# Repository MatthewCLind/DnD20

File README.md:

# DnD20
WiFi Connected electronic die for enhancing online DnD gameplaying

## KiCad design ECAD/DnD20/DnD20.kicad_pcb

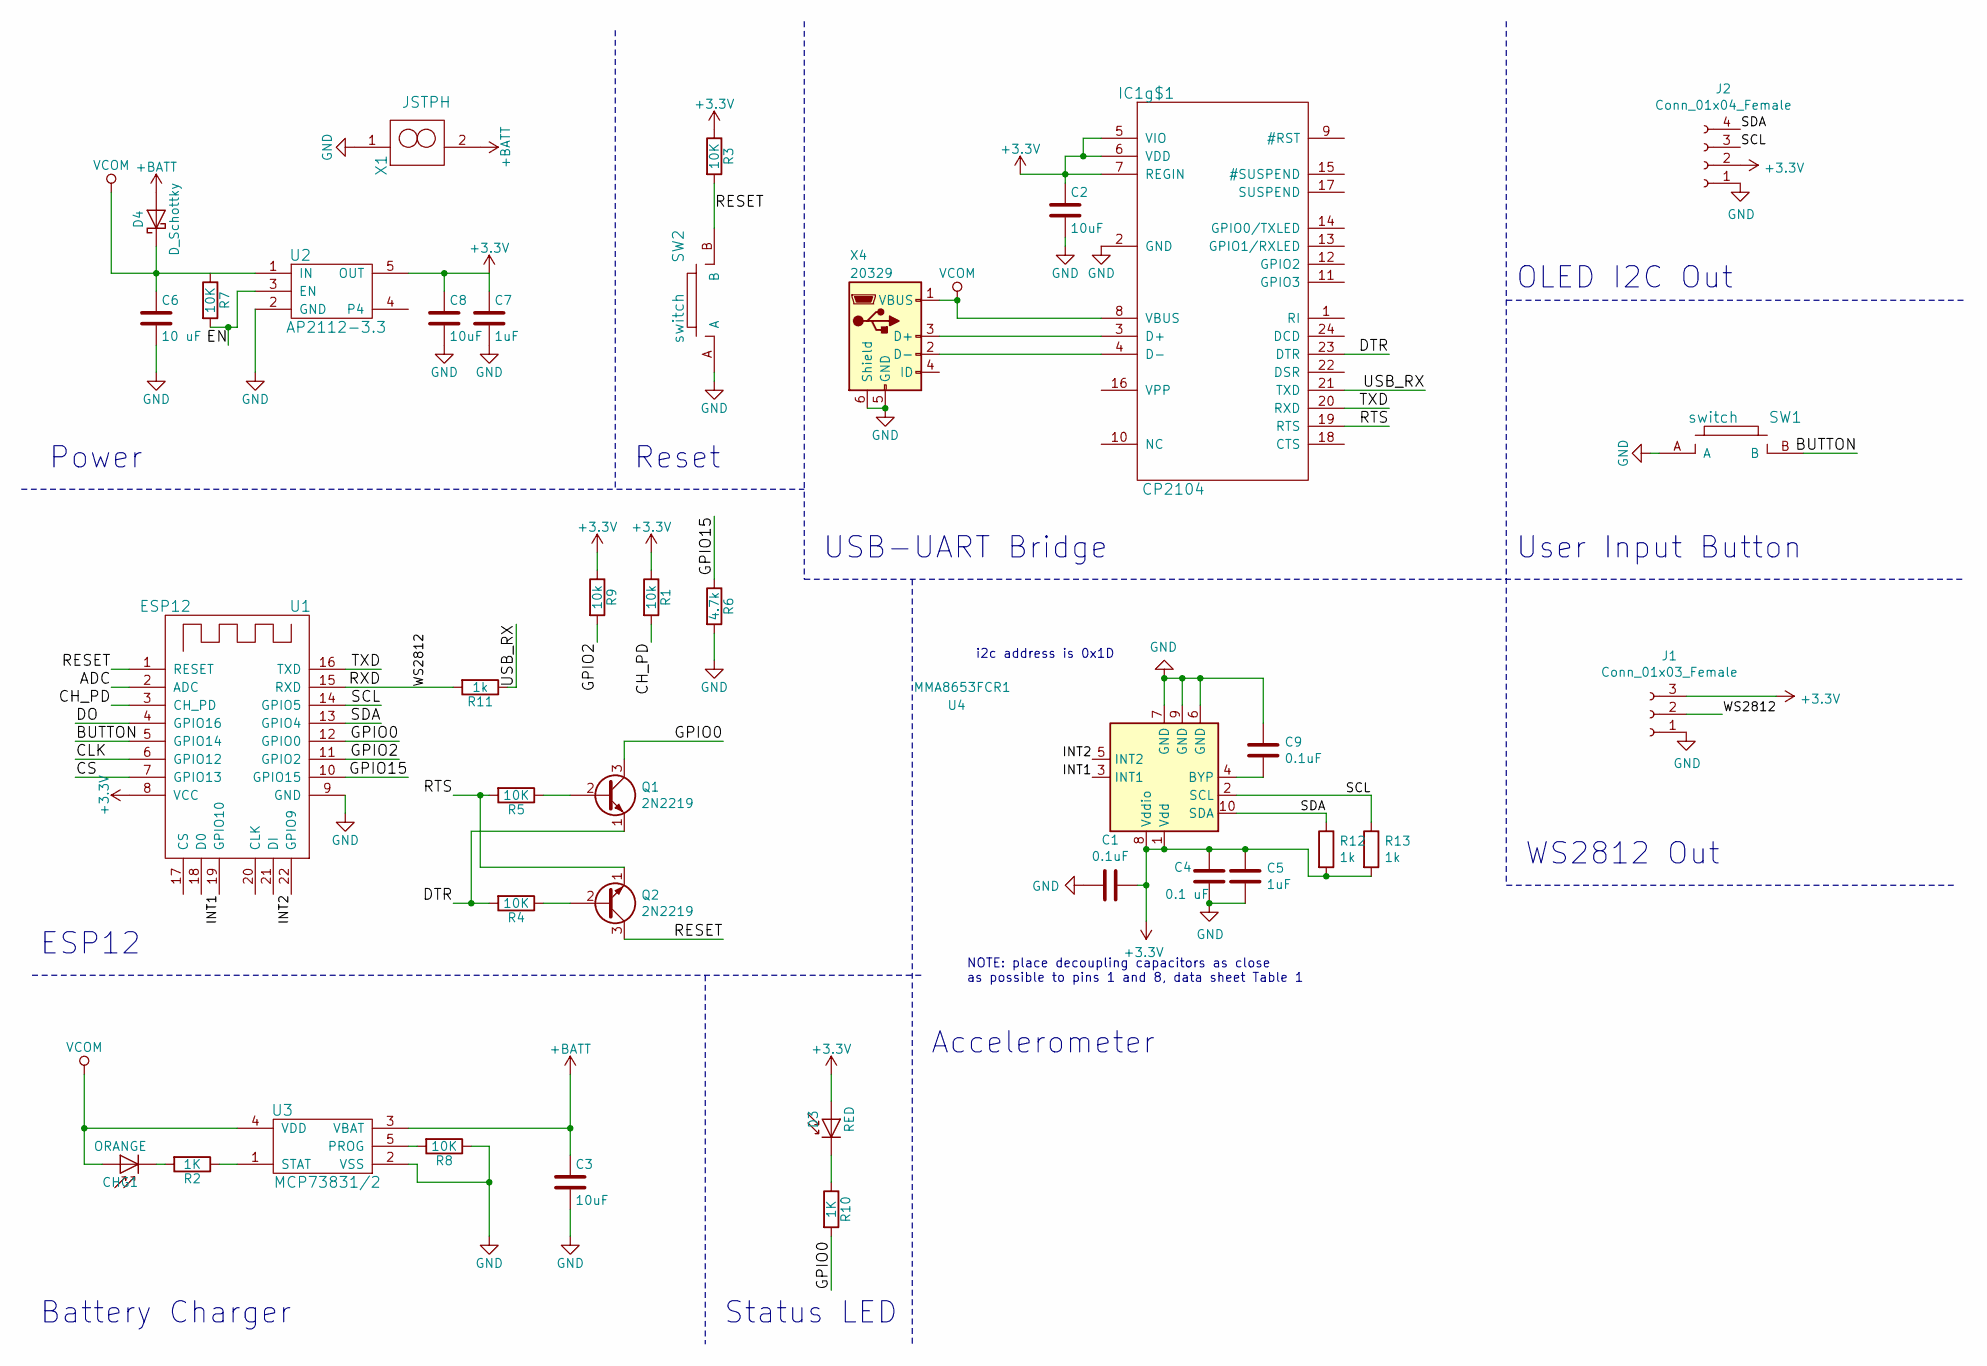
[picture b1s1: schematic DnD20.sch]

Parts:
C1, C9: 0.1uF; C_0805_2012Metric
C2, C3, C8: 10uF; C_0805_2012Metric
C4: 0.1 uF; C_0805_2012Metric
C5, C7: 1uF; C_0805_2012Metric
C6: 10 uF; C_0805_2012Metric
CHG1: ORANGE; LED_0603_1608Metric
D3: RED; LED_0603_1608Metric
D4: D_Schottky; D_T-1_P5.08mm_Horizontal
IC1g$1: CP2104; QFN-24-1EP_4x4mm_P0.5mm_EP2.7x2.7mm
J1: Conn_01x03_Female; PinHeader_1x03_P2.54mm_Vertical
J2: Conn_01x04_Female; PinHeader_1x04_P2.54mm_Vertical
Q1, Q2: 2N2219; TO-39-3
R1, R9: 10k; R_0805_2012Metric
R2, R10: 1K; R_0805_2012Metric
R3, R4, R5, R7, R8: 10K; R_0805_2012Metric
R6: 4.7k; R_0805_2012Metric
R11, R12, R13: 1k; R_0805_2012Metric
SW1, SW2: switch; clicky_button
U1: ESP12; ESP-12E_SMD
U2: AP2112-3.3; SOT-23-5_HandSoldering
U3: MCP73831/2; SOT-23-5_HandSoldering
U4: MMA8653FCR1; DFN-10_2x2mm_P0.4mm
X1: JSTPH; JST_PH_S2B-PH-K_1x02_P2.00mm_Horizontal
X4: 20329; USB_Micro-B_Wuerth_629105150521

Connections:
+3V3: C1.1, C2.1, C4.2, C5.1, C7.1, C8.1, D3.2 (A), IC1g$1.5 (VIO), IC1g$1.6 (VDD), IC1g$1.7 (REGIN), J1.3, J2.2, R1.1, R3.1, R9.1, R12.2, R13.2, U1.8 (VCC), U2.5 (OUT), U4.1 (Vdd), U4.8 (Vddio)
+BATT: C3.1, D4.2 (A), U3.3 (VBAT), X1.2
/ADC: U1.2 (ADC)
/BUTTON: SW1.B, U1.5 (GPIO14)
/CH_PD: R1.2, U1.3 (CH_PD)
/CLK: U1.6 (GPIO12)
/CS: U1.7 (GPIO13)
/DO: U1.4 (GPIO16)
/DTR: IC1g$1.23 (DTR), Q1.1 (E), R4.2
/EN: R7.2, U2.3 (EN)
/GPIO0: Q1.3 (C), R10.2, U1.12 (GPIO0)
/GPIO2: R9.2, U1.11 (GPIO2)
/GPIO15: R6.1, U1.10 (GPIO15)
/INT1: U1.19 (GPIO10), U4.3 (INT1)
/INT2: U1.22 (GPIO9), U4.5 (INT2)
/RESET: Q2.3 (C), R3.2, SW2.B, U1.1 (RESET)
/RTS: IC1g$1.19 (RTS), Q2.1 (E), R5.2
/RXD: J1.2, R11.2, U1.15 (RXD)
/SCL: J2.3, R13.1, U1.14 (GPIO5), U4.2 (SCL)
/SDA: J2.4, R12.1, U1.13 (GPIO4), U4.10 (SDA)
/TXD: IC1g$1.20 (RXD), U1.16 (TXD)
/USB_RX: IC1g$1.21 (TXD), R11.1
GND: C1.2, C2.2, C3.2, C4.1, C5.2, C6.2, C7.2, C8.2, C9.1, IC1g$1.2 (GND), J1.1, J2.1, R6.2, R8.1, SW1.A, SW2.A, U1.9 (GND), U2.2 (GND), U3.2 (VSS), U4.6 (GND), U4.7 (GND), U4.9 (GND), X1.1, X4.5 (GND), X4.6 (Shield)
unnamed: C9.2, U4.4 (BYP)
unnamed: CHG1.1 (K), R2.2
unnamed: D3.1 (K), R10.1
unnamed: IC1g$1.3 (D+), X4.3 (D+)
unnamed: IC1g$1.4 (D-), X4.2 (D-)
unnamed: Q1.2 (B), R5.1
unnamed: Q2.2 (B), R4.1
unnamed: R2.1, U3.1 (STAT)
unnamed: R8.2, U3.5 (PROG)
VCOM: C6.1, CHG1.2 (A), D4.1 (K), IC1g$1.8 (VBUS), U2.1 (IN), U3.4 (VDD), X4.1 (VBUS)

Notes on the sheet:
NOTE: place decoupling capacitors as close as possible to pins 1 and 8, data sheet Table 1
i2c address is 0x1D
Power
ESP12
Battery Charger
USB-UART Bridge
OLED I2C Out
User Input Button
WS2812 Out
Accelerometer
Reset
Status LED

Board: 2 copper layers, 38 parts (2 on the bottom side), 29 nets, no tracks yet.

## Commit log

2018-10-05 dev-log-1
2018-10-05 added first whiteboard sketch
2018-10-05 intial firmware outline
2018-10-05 initial bare-bones webpage html
2018-10-05 added LED feature
2018-10-05 added LEDs and fixedcompiler errors
2018-10-06 updated to work with adafruit feather huzzah
2018-10-06 added second dlog and folders
2018-10-07 added OLED and WiFi code
2018-10-07 changed file extensions to .md
2018-10-08 accelerometer, https request
2018-10-08 formatting
2018-10-08 removed redundant device initalisor
2018-10-08 added Benchtop Prototype showcase
2018-10-08 fixed italics
2018-10-08 added spaces
2018-10-09 fixed date
2018-10-09 new log
2018-10-09 new design drawing
2018-10-09 fixed picture link
2018-10-09 changed to .jpg
2018-10-10 adding MCAD files
2018-10-10 capt's log and renamed screenshots
2018-10-10 image linking ... always
2018-10-10 link image
2018-10-10 better image
2018-10-11 created rubber suspension and PCB
2018-10-11 created kicad, pcb outline, captains log
2018-10-12 PCB schematic, board, and captains log
2018-10-12 captains log
2018-10-12 schematic
2018-10-13 created shell.svg
2018-10-13 captains log 10.12.2018
2018-10-13 0 - padding for alphabetic sort
2018-10-13 added new inputs
2018-10-14 captain's log Oct 13
2018-10-14 added magic 8 ball, merged wifi config to progmode
2018-10-14 added more fields
2018-11-26 Refactored firmware before removing accelerometer
2018-11-29 3 modes. no push-button. not working
2018-12-03 functional EEPROM, button, OLED, neopixel, wifi
